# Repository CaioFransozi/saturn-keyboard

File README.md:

## Credits
Inspiration for the keyboard came from the [corney island](https://github.com/ceoloide/corney-island) keyboard project. Made following the [FlatFootFox guide](https://flatfootfox.com/ergogen-introduction/)

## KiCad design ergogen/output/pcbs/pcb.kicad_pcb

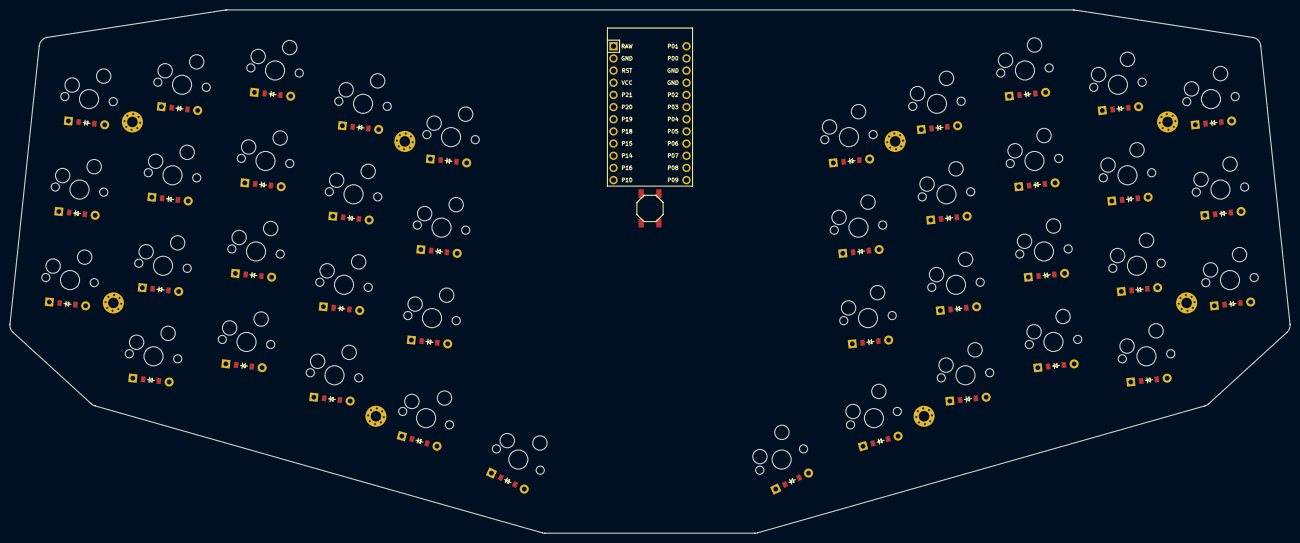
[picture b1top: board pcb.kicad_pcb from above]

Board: 2 copper layers, 267.3 x 109.3 mm, 90 parts (0 on the bottom side), 60 nets, no tracks yet.

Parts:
B1: SW_TACT_ALPS_SKQGABE010
D1, D2, D3, D4, D5, D6, D7, D8, D9, D10, D11, D12, D13, D14, D15, D16, D17, D18, D19, D20, D21, D22, D23, D24, D25, D26, D27, D28, D29, D30, D31, D32, D33, D34, D35, D36, D37, D38, D39, D40: ComboDiode
MCU1: ProMicro
S1, S2, S3, S4, S5, S6, S7, S8, S9, S10, S11, S12, S13, S14, S15, S16, S17, S18, S19, S20, S21, S22, S23, S24, S25, S26, S27, S28, S29, S30, S31, S32, S33, S34, S35, S36, S37, S38, S39, S40: MX
_1, _2, _3, _4, _5, _6, _7, _8: MountingHole_2.2mm_M2_Pad_Via

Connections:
GND: B1.1, MCU1.2, MCU1.15, MCU1.16
P0: MCU1.14, S21.1, S22.1, S23.1
P1: MCU1.13, S1.1, S2.1, S3.1
P2: MCU1.17, S24.1, S25.1, S26.1, S27.1
P3: MCU1.18, S28.1, S29.1, S30.1, S31.1
P4: MCU1.19, S32.1, S33.1, S34.1, S35.1, S39.1
P5: MCU1.20, S36.1, S37.1, S38.1, S40.1
P6: D23.1, D27.1, D31.1, D35.1, D38.1, MCU1.21
P7: D22.1, D26.1, D30.1, D34.1, D37.1, MCU1.22
P8: D21.1, D25.1, D29.1, D33.1, D36.1, MCU1.23
P9: D24.1, D28.1, D32.1, D39.1, D40.1, MCU1.24
P10: D4.1, D8.1, D12.1, D19.1, D20.1, MCU1.12
P14: D2.1, D6.1, D10.1, D14.1, D17.1, MCU1.10
P15: D3.1, D7.1, D11.1, D15.1, D18.1, MCU1.9
P16: D1.1, D5.1, D9.1, D13.1, D16.1, MCU1.11
P18: MCU1.8, S16.1, S17.1, S18.1, S20.1
P19: MCU1.7, S12.1, S13.1, S14.1, S15.1, S19.1
P20: MCU1.6, S8.1, S9.1, S10.1, S11.1
P21: MCU1.5, S4.1, S5.1, S6.1, S7.1
RST: B1.2, MCU1.3
index_bottom: D13.2, S13.2
index_home: D14.2, S14.2
index_mod: D12.2, S12.2
index_top: D15.2, S15.2
inner_bottom: D16.2, S16.2
inner_home: D17.2, S17.2
inner_top: D18.2, S18.2
layer_main: D20.2, S20.2
main_main: D19.2, S19.2
middle_bottom: D9.2, S9.2
middle_home: D10.2, S10.2
middle_mod: D8.2, S8.2
middle_top: D11.2, S11.2
mirror_index_bottom: D33.2, S33.2
mirror_index_home: D34.2, S34.2
mirror_index_mod: D32.2, S32.2
mirror_index_top: D35.2, S35.2
mirror_inner_bottom: D36.2, S36.2
mirror_inner_home: D37.2, S37.2
mirror_inner_top: D38.2, S38.2
mirror_layer_main: D40.2, S40.2
mirror_main_main: D39.2, S39.2
mirror_middle_bottom: D29.2, S29.2
mirror_middle_home: D30.2, S30.2
mirror_middle_mod: D28.2, S28.2
mirror_middle_top: D31.2, S31.2
mirror_pinky_bottom: D21.2, S21.2
mirror_pinky_home: D22.2, S22.2
mirror_pinky_top: D23.2, S23.2
mirror_ring_bottom: D25.2, S25.2
mirror_ring_home: D26.2, S26.2
mirror_ring_mod: D24.2, S24.2
mirror_ring_top: D27.2, S27.2
pinky_bottom: D1.2, S1.2
pinky_home: D2.2, S2.2
pinky_top: D3.2, S3.2
ring_bottom: D5.2, S5.2
ring_home: D6.2, S6.2
ring_mod: D4.2, S4.2
ring_top: D7.2, S7.2

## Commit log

2026-02-19 Updated gitignore
2026-02-19 added mounting holes to pcb design
